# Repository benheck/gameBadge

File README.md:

# gameBadge
Source code and test examples for Midwest Gaming Classic 2021 Workshop project "gameBadge"

[email instructions.docx](https://github.com/benheck/gameBadge/files/7478824/email.instructions.docx)

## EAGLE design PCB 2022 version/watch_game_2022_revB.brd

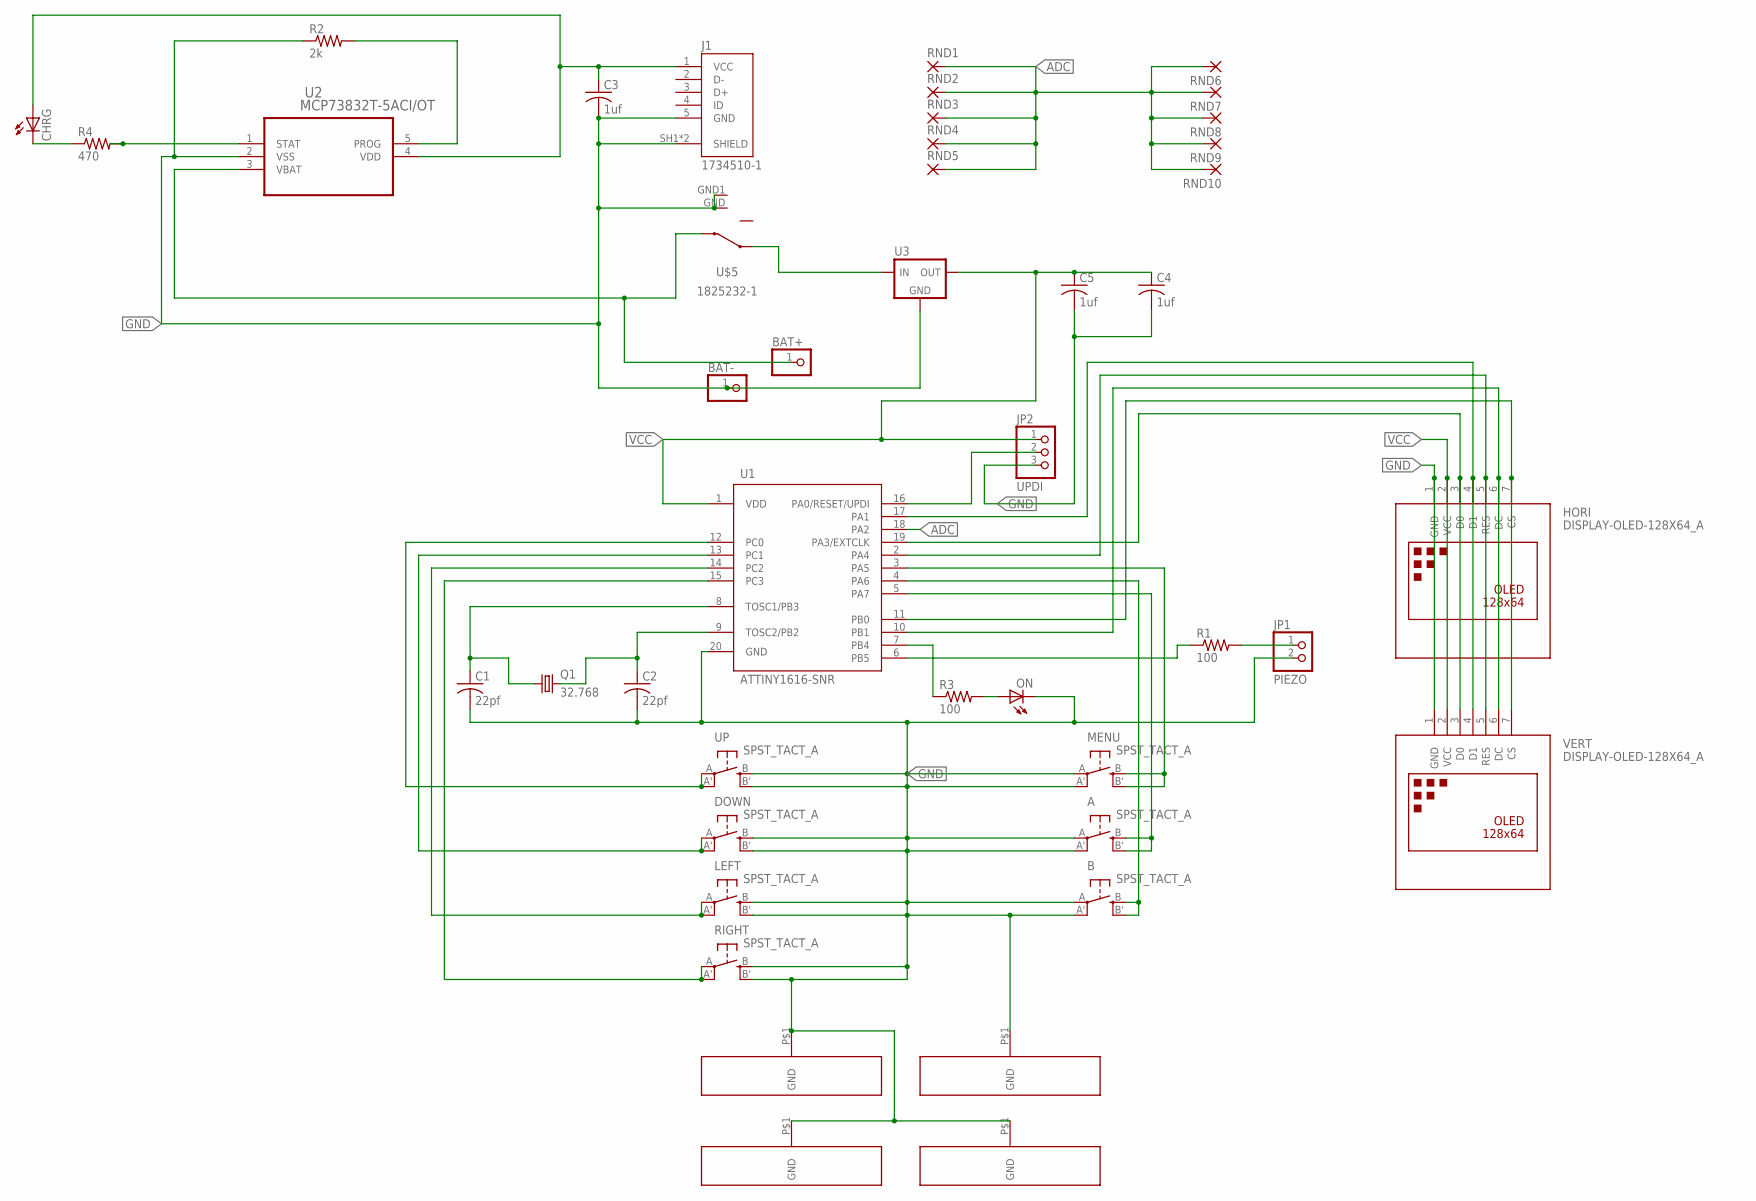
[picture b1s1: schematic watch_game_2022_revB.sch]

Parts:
A: SPST_TACT_A; EVQ-Q2_A
B: SPST_TACT_A; EVQ-Q2_A
BAT+: PINHD-1X1; 1X01
BAT-: PINHD-1X1; 1X01
C1, C2: 22pf; C0805
C3, C4, C5: 1uf; C0805
CHRG: LED3MM
DOWN: SPST_TACT_A; EVQ-Q2_A
HORI: DISPLAY-OLED-128X64_A
J1: 1734510-1; TE_1734510-1
JP1: PIEZO; 1X02
JP2: UPDI; 1X03
LEFT: SPST_TACT_A; EVQ-Q2_A
MENU: SPST_TACT_A; EVQ-Q2_A
ON: LED5MM
Q1: 32.768; TC26H
R1, R3: 100; M0805
R2: 2k; M0805
R4: 470; M0805
RIGHT: SPST_TACT_A; EVQ-Q2_A
RND1, RND2, RND3, RND4, RND5, RND6, RND7, RND8, RND9, RND10: SMD5; SMD2,54-5,08
U1: ATTINY1616-SNR; SOIC127P1032X265-20N
U2: MCP73832T-5ACI/OT; SOT95P300X145-5N
U3: LF50CDT; DPAK
U$5: 1825232-1
U$6, U$7, U$8, U$9: GND_STRIP_600MIL; GND_PADS_2
UP: SPST_TACT_A; EVQ-Q2_A
VERT: DISPLAY-OLED-128X64_A

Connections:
ADC: RND1.1, RND2.1, RND3.1, RND4.1, RND5.1, RND6.1, RND7.1, RND8.1, RND9.1, RND10.1, U1.18 (PA2)
GND: A.A, A.A' (P1), B.A, B.A' (P1), BAT-.1, C1.2, C2.2, C3.2, C4.2, C5.2, DOWN.B (S), DOWN.B' (S1), HORI.1 (GND), J1.5 (GND), J1.SH1 (SHIELD), J1.SH2 (SHIELD), JP1.2, JP2.3, LEFT.B (S), LEFT.B' (S1), MENU.A, MENU.A' (P1), ON.K (C), R2.1, RIGHT.B (S), RIGHT.B' (S1), U1.20 (GND), U2.2 (VSS), U3.4 (GND), U$5.GND, U$5.GND1, U$6.P$1, U$7.P$1, U$8.P$1, U$9.P$1, UP.B (S), UP.B' (S1), VERT.1 (GND)
unnamed: U1.12 (PC0), UP.A, UP.A' (P1)
unnamed: DOWN.A, DOWN.A' (P1), U1.13 (PC1)
unnamed: LEFT.A, LEFT.A' (P1), U1.14 (PC2)
unnamed: RIGHT.A, RIGHT.A' (P1), U1.15 (PC3)
unnamed: B.B (S), B.B' (S1), U1.4 (PA6)
unnamed: HORI.3 (D0), U1.19 (PA3/EXTCLK), VERT.3 (D0)
unnamed: R3.1, U1.7 (PB4)
unnamed: JP1.1, R1.2
unnamed: C3.1, CHRG.A, J1.1 (VCC), U2.4 (VDD)
unnamed: U3.1 (VIN), U$5.3
unnamed: R4.2, U2.1 (STAT)
unnamed: BAT+.1, U2.3 (VBAT), U$5.2
unnamed: JP2.2, U1.16 (PA0/RESET/UPDI)
unnamed: HORI.4 (D1), U1.17 (PA1), VERT.4 (D1)
unnamed: HORI.5 (RES), U1.2 (PA4), VERT.5 (RES)
unnamed: MENU.B (S), MENU.B' (S1), U1.3 (PA5)
unnamed: ON.A, R3.2
unnamed: A.B (S), A.B' (S1), U1.5 (PA7)
unnamed: HORI.7 (CS), U1.11 (PB0), VERT.7 (CS)
unnamed: HORI.6 (DC), U1.10 (PB1), VERT.6 (DC)
unnamed: R1.1, U1.6 (PB5)
unnamed: C1.1, Q1.1, U1.8 (TOSC1/PB3)
unnamed: C2.1, Q1.2, U1.9 (TOSC2/PB2)
unnamed: R2.2, U2.5 (PROG)
unnamed: CHRG.K (C), R4.1
VCC: C4.1, C5.1, HORI.2 (VCC), JP2.1, U1.1 (VDD), U3.3 (VOUT), VERT.2 (VCC)

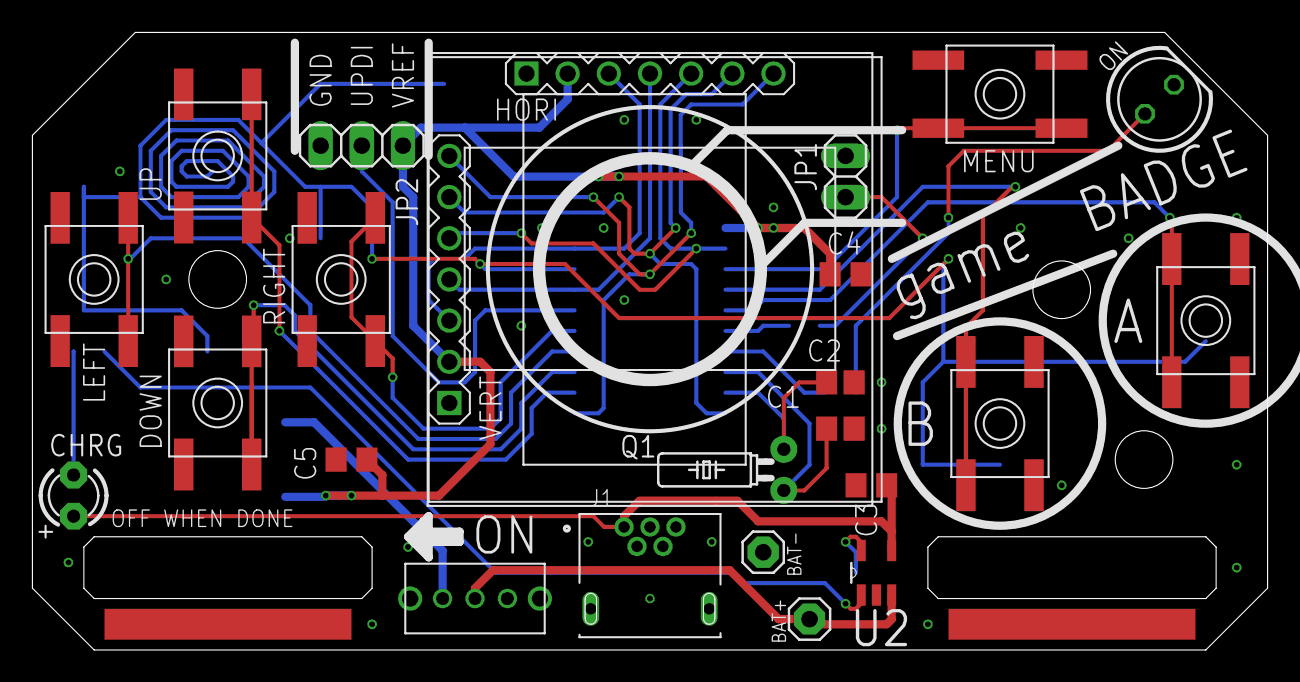
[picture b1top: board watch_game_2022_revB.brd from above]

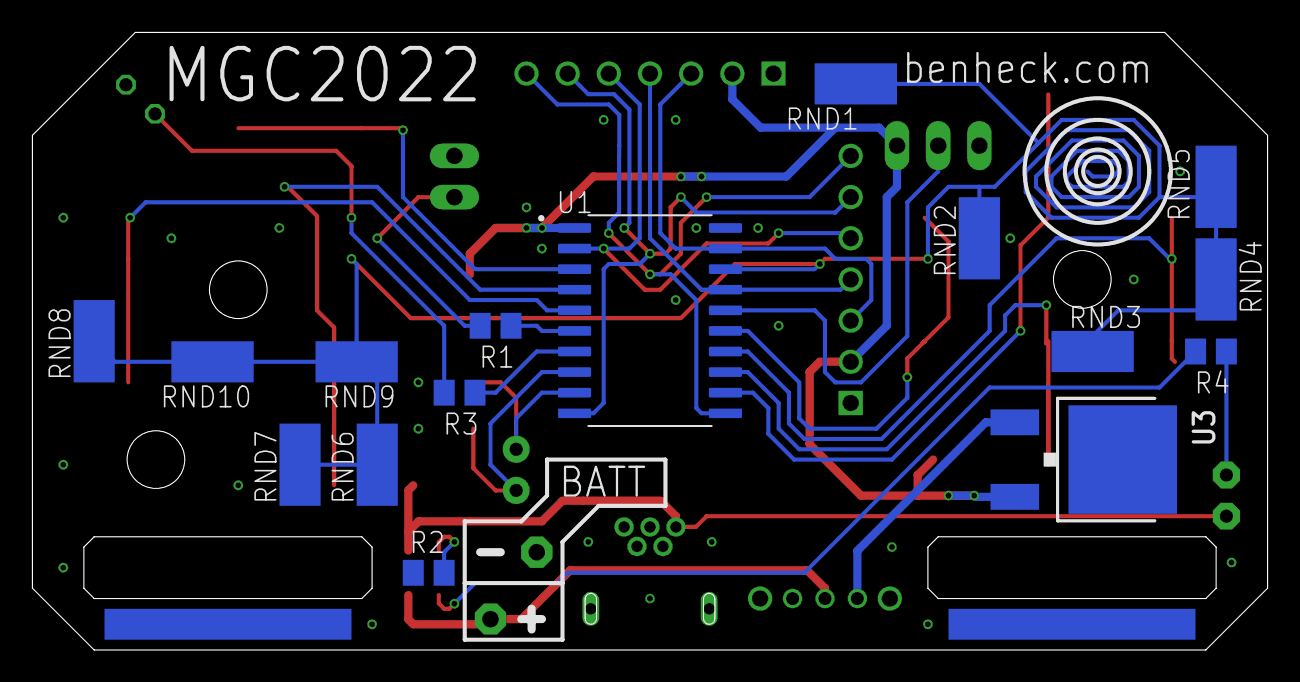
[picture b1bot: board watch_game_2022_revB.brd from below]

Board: 2 copper layers, 76.2 x 38.1 mm, 44 parts (18 on the bottom side), 28 nets.

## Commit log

2021-10-09 Initial upload
2021-10-09 Docs and changes
2021-10-09 Added gfx source and PCB
2021-10-30 Added Moon Force game
2021-10-30 File shuffling
2021-10-30 Added graphics
2021-11-03 Crunch
2021-11-03 more stuff
2021-11-04 MOAR updatez
2021-11-04 Added assembly diagram
2021-11-05 pre-MGC
2022-02-16 MGC changes
2022-03-11 Easy tweaks
2022-03-14 Added new 2022 version of PCB. Changes to regulator and charge controller
2022-03-14 Changed graphic date to 2022
2022-04-27 Adding in-progress SAMD11C version
2022-05-12 ARM conversion
2022-11-27 Starting color version

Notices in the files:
parts and their libraries:
diy-modules: Released under the Creative Commons Attribution 4.0 International License: http://creativecommons.org/licenses/by/4.0
